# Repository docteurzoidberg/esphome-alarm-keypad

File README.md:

# Esphome Alarm Keypad

! README IN PROGRESS !

The Alarm Keypad is an interface to the Home Assistant Alarm Control Panel

//TODO: insert link here of ha alarm integration

Goal is to have a nice alarm control panel with lights, displays, rfid tag reader and a backup keypad to arm/disarm the Home Assistant alarm.

## Prototype video

## Features

- 13 key keyboard with mechanical switches . behind a pcf8574 i2c i/o expander
- per key adressable rgb backlight (13)
- pn532 rfid reader
- adressable led strip for case backlight
- adressable led ring for rfid feedback
- two 4 character alphanum displays with ht16k33 backpacks
- RTTTL sound output

## Hardware:

kicad/ contain the custom made pcb with all i/o from and to the esp, integrating the keypad with per key smd rgb backlight.

## Software:

//TODO: link to my-esphome github repo

### boot

    loading sequence on leds and screen

### connected

    show alarm state (armed/disarmed and so on)

### disconnected

    show "ERROR"

### rfid scan

    animate rfid led ring
    HA tag scanned service, changing alarm state if correct tag?

### key press

    flash key backlight in one color
    enter typing state

### typing

    show "code ?" + asterisk each pressed key until 4
    when 4 (allowed) keys pressed enter code check state
    start timer to enter typing timeout if no key pressed in X seconds

### typing timeout

    do something animated with case and keypad leds
    return back to alarm state mode

### code check

    display "check..." until we got a state change in HA alarm, or entering a 5sec timeout
    do something animated with case and keypad leds
### code check timeout

    HA alarm state didn't changed so the code is wrong or there is a problem
    display "FAIL" for 3 sec and go back to alarm state mode
    do something animated with case and keypad leds

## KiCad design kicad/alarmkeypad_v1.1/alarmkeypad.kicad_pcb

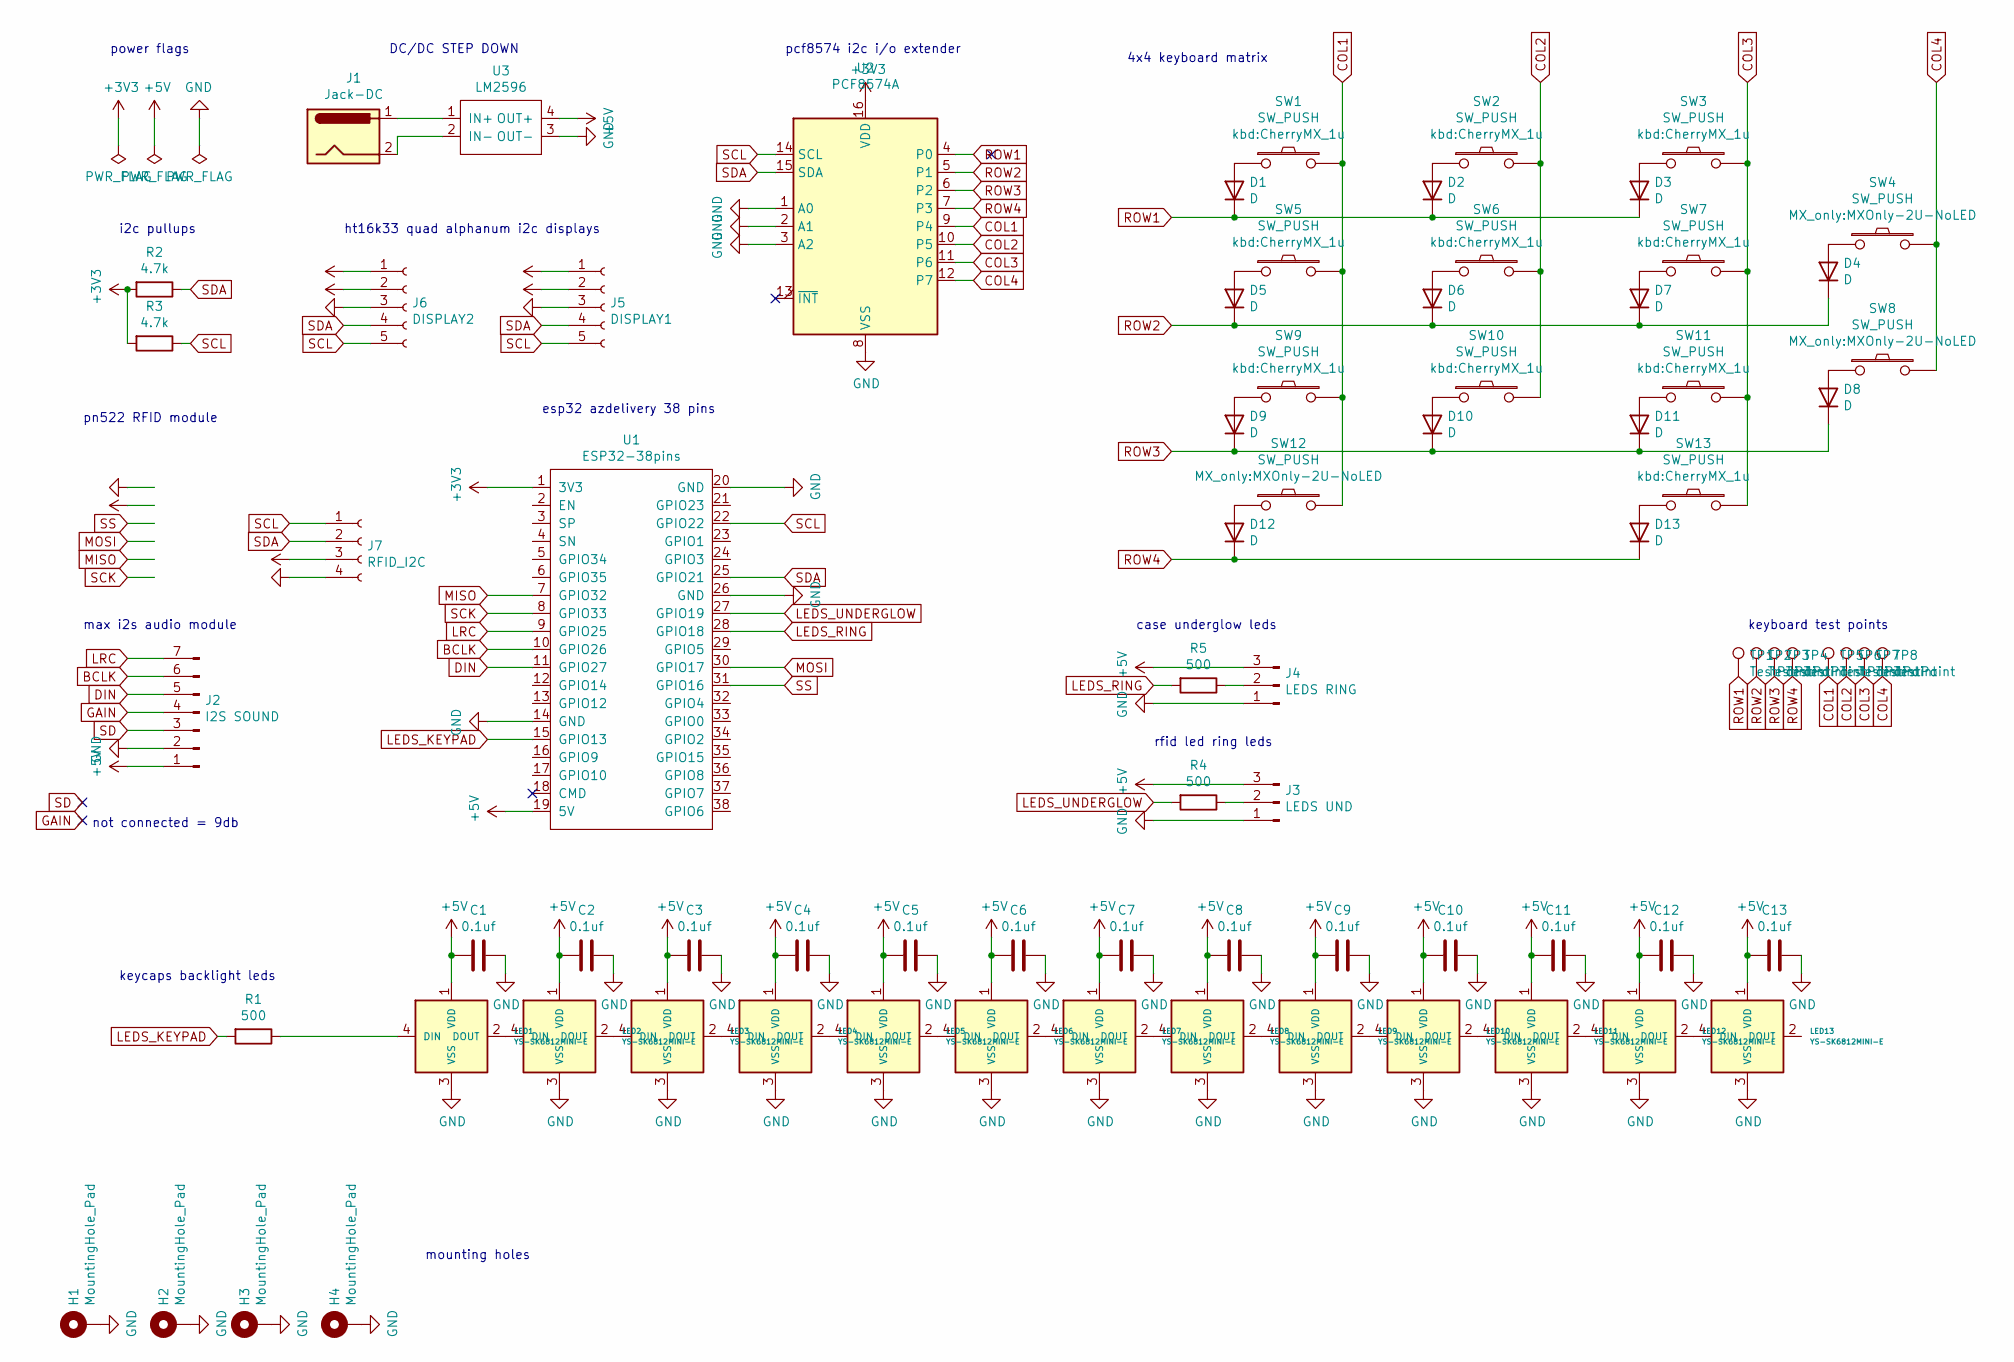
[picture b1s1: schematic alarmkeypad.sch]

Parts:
C1, C2, C3, C4, C5, C6, C7, C8, C9, C10, C11, C12, C13: 0.1uf; C_0805_HandSoldering
D1, D2, D3, D4, D5, D6, D7, D8, D9, D10, D11, D12, D13: D; D_0805
H1, H2, H3, H4: MountingHole_Pad; MountingHole_3.2mm_M3_Pad_Via
J1: Jack-DC; JACK_ALIM
J2: I2S SOUND; Pin_Header_Straight_1x07_Pitch2.54mm
J3: LEDS UND; Pin_Header_Angled_1x03_Pitch2.54mm
J4: LEDS RING; Pin_Header_Angled_1x03_Pitch2.54mm
J5: DISPLAY1; Pin_Header_Straight_1x05_Pitch2.54mm
J6: DISPLAY2; Pin_Header_Straight_1x05_Pitch2.54mm
J7: RFID_I2C; Pin_Header_Straight_1x04_Pitch2.54mm
LED1, LED2, LED3, LED4, LED5, LED6, LED7, LED8, LED9, LED10, LED11, LED12, LED13: YS-SK6812MINI-E
R1, R4, R5: 500; R_0805_HandSoldering
R2, R3: 4.7k; R_0805_HandSoldering
SW1, SW2, SW3, SW5, SW6, SW7, SW9, SW10, SW11, SW13: SW_PUSH; CherryMX_1u
SW4, SW8, SW12: SW_PUSH; MXOnly-2U-NoLED
TP1, TP2, TP3, TP4, TP5, TP6, TP7, TP8: TestPoint; TestPoint_Pad_D1.5mm
U1: ESP32-38pins; esp32 38pin azdelivery
U2: PCF8574A; SO-16-L
U3: LM2596; LM2596 module

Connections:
+3V3: J5.1, J6.1, R2.2, R3.2, U1.1 (3V3), U2.16 (VDD)
+5V: C1.1, C2.1, C3.1, C4.1, C5.1, C6.1, C7.1, C8.1, C9.1, C10.1, C11.1, C12.1, C13.1, J2.1, J3.3, J4.3, J5.2, J6.2, J7.3, LED1.1 (VDD), LED2.1 (VDD), LED3.1 (VDD), LED4.1 (VDD), LED5.1 (VDD), LED6.1 (VDD), LED7.1 (VDD), LED8.1 (VDD), LED9.1 (VDD), LED10.1 (VDD), LED11.1 (VDD), LED12.1 (VDD), LED13.1 (VDD), U1.19 (5V), U3.4 (OUT+)
BCLK: J2.6, U1.10 (GPIO26)
COL1: SW1.2, SW5.2, SW9.2, SW12.2, TP5.1, U2.9 (P4)
COL2: SW2.2, SW6.2, SW10.2, TP6.1, U2.10 (P5)
COL3: SW3.2, SW7.2, SW11.2, SW13.2, TP7.1, U2.11 (P6)
COL4: SW4.2, SW8.2, TP8.1, U2.12 (P7)
DIN: J2.5, U1.11 (GPIO27)
GAIN: J2.4
GND: C1.2, C2.2, C3.2, C4.2, C5.2, C6.2, C7.2, C8.2, C9.2, C10.2, C11.2, C12.2, C13.2, H1.1, H2.1, H3.1, H4.1, J2.2, J3.1, J4.1, J5.3, J6.3, J7.4, LED1.3 (VSS), LED2.3 (VSS), LED3.3 (VSS), LED4.3 (VSS), LED5.3 (VSS), LED6.3 (VSS), LED7.3 (VSS), LED8.3 (VSS), LED9.3 (VSS), LED10.3 (VSS), LED11.3 (VSS), LED12.3 (VSS), LED13.3 (VSS), U1.14 (GND), U1.20 (GND), U1.26 (GND), U2.1 (A0), U2.2 (A1), U2.3 (A2), U2.8 (VSS), U3.3 (OUT-)
LEDS_KEYPAD: R1.2, U1.15 (GPIO13)
LEDS_RING: R5.2, U1.28 (GPIO18)
LEDS_UNDERGLOW: R4.2, U1.27 (GPIO19)
LRC: J2.7, U1.9 (GPIO25)
MISO: U1.7 (GPIO32)
MOSI: U1.30 (GPIO17)
unnamed: D1.2 (A), SW1.1
unnamed: D2.2 (A), SW2.1
unnamed: D3.2 (A), SW3.1
unnamed: D4.2 (A), SW4.1
unnamed: D5.2 (A), SW5.1
unnamed: D6.2 (A), SW6.1
unnamed: D7.2 (A), SW7.1
unnamed: D8.2 (A), SW8.1
unnamed: D9.2 (A), SW9.1
unnamed: D10.2 (A), SW10.1
unnamed: D11.2 (A), SW11.1
unnamed: D12.2 (A), SW12.1
unnamed: D13.2 (A), SW13.1
unnamed: J1.1, U3.1 (IN+)
unnamed: J1.2, U3.2 (IN-)
unnamed: J3.2, R4.1
unnamed: J4.2, R5.1
unnamed: LED1.2 (DOUT), LED2.4 (DIN)
unnamed: LED1.4 (DIN), R1.1
unnamed: LED2.2 (DOUT), LED3.4 (DIN)
unnamed: LED3.2 (DOUT), LED4.4 (DIN)
unnamed: LED4.2 (DOUT), LED5.4 (DIN)
unnamed: LED5.2 (DOUT), LED6.4 (DIN)
unnamed: LED6.2 (DOUT), LED7.4 (DIN)
unnamed: LED7.2 (DOUT), LED8.4 (DIN)
unnamed: LED8.2 (DOUT), LED9.4 (DIN)
unnamed: LED10.2 (DOUT), LED11.4 (DIN)
unnamed: LED9.2 (DOUT), LED10.4 (DIN)
unnamed: LED11.2 (DOUT), LED12.4 (DIN)
unnamed: LED12.2 (DOUT), LED13.4 (DIN)
ROW1: D1.1 (K), D2.1 (K), D3.1 (K), TP1.1, U2.4 (P0)
ROW2: D4.1 (K), D5.1 (K), D6.1 (K), D7.1 (K), TP2.1, U2.5 (P1)
ROW3: D8.1 (K), D9.1 (K), D10.1 (K), D11.1 (K), TP3.1, U2.6 (P2)
ROW4: D12.1 (K), D13.1 (K), TP4.1, U2.7 (P3)
SCK: U1.8 (GPIO33)
SCL: J5.5, J6.5, J7.1, R3.1, U1.22 (GPIO22), U2.14 (SCL)
SD: J2.3
SDA: J5.4, J6.4, J7.2, R2.1, U1.25 (GPIO21), U2.15 (SDA)
SS: U1.31 (GPIO16)

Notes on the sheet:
DC/DC STEP DOWN
i2c pullups
ht16k33 quad alphanum i2c displays
4x4 keyboard matrix
keycaps backlight leds
case underglow leds
rfid led ring leds
keyboard test points
mounting holes
power flags
not connected = 9db
max i2s audio module
pn522 RFID module
pcf8574 i2c i/o extender
esp32 azdelivery 38 pins

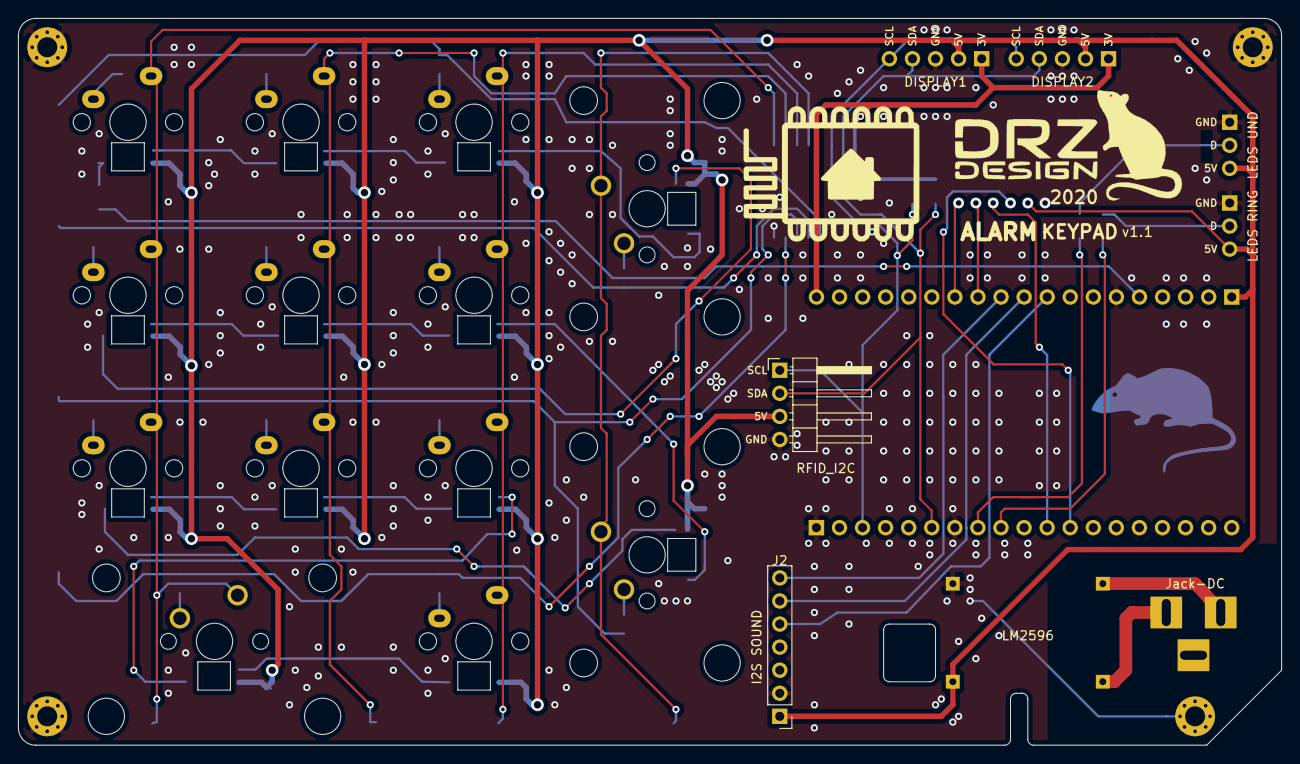
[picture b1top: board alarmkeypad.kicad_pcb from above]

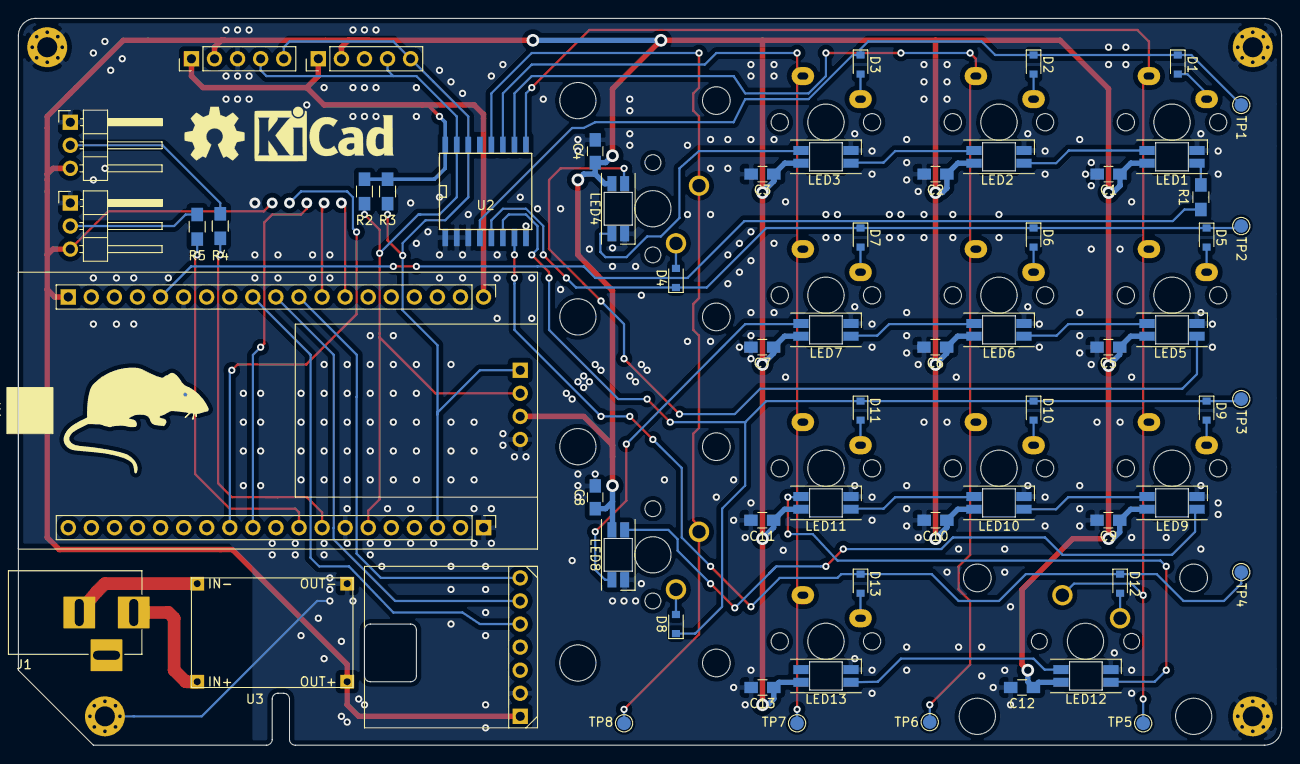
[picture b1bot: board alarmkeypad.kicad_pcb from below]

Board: 2 copper layers, 139.0 x 79.9 mm, 79 parts (60 on the bottom side), 49 nets.

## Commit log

2020-11-06 first
2020-11-06 add some renders
2021-01-29 Alarmkeypad v0 pcb final, and working esphome sample
2021-01-29 readme
2021-01-29 forgot file
